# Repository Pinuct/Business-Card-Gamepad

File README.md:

# Business-Card-Gamepad
Hardware and software files for the Business Card Gamepad.

**IF YOU WANT MORE DETAILS ABOUT THE PROJET  ----->  [HACKADAY.IO](https://hackaday.io/project/28516-business-card-gamepad) <-----**

It contains all necesary files to make a Business Card Gamepad. With capacitive touch buttons and USB interface thought a USB micro B PCB connector. If you connect it to a PC with a USB to micro USB cable, it acts as a joystick for the host PC.

# Folders

## Arduino Code

Contains the Arduino project for the gamepad code of the business card and a touch button library (used to detect capacitive button press). The code of the .ino is simple and self explanatory, it it initializes the joystick library and the touch buttons library and loops throught the readings of the touch buttons, when there is a press it send a joystick event to the PC.

If you want to compile this code you will need to include two more libraries. This code can't not work without the great libreries that Martin Pittermann ([ADCTouch library](https://github.com/martin2250/ADCTouch)) and Matthew Heironimus ([ArduinoJoystickLibrary](https://github.com/MHeironimus/ArduinoJoystickLibrary)) did. So thanks to them to make this posible.

## Eagle PCB 

Contains an Eagle 7.50 project for the business card PCB. If you want to make it, is necesary to use a PCB of 0.6 mm thickness, needed for the USB PCB connector to be able to connect to a USB micro b cable.

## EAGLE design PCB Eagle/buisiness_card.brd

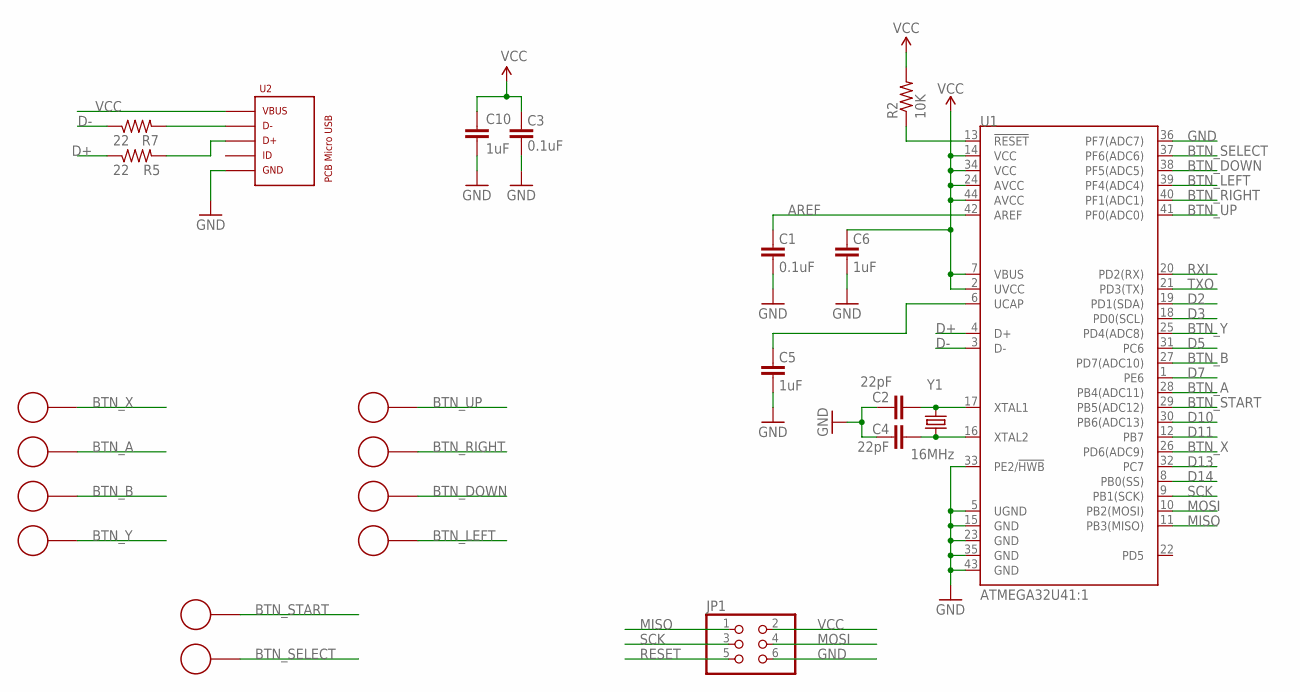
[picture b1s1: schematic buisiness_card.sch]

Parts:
B1, B2, B3, B4, B5, B6, B7, B8, B9, B10: CAPACITIVE_BUTTON; ROUND_CAP_BUTTON
C1, C3: 0.1uF; 0603-CAP
C2, C4: 22pF; 0603-CAP
C5, C6, C10: 1uF; 0603-CAP
JP1: PINHD-2X3; 2X03
R2: 10K; 0603-RES
R5, R7: 22; 0603-RES
U1: ATMEGA32U41:1; QFN-44-NOPAD_1:1
U2: PCB_MICRO_USB_BSS_2; USB_TYPE_B_SS_2
Y1: 16MHz; CRYSTAL-SMD-5X3

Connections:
AREF: C1.2, U1.42 (AREF)
BTN_A: B2.P$1, U1.28 (PB4(ADC11))
BTN_B: B3.P$1, U1.27 (PD7(ADC10))
BTN_DOWN: B7.P$1, U1.38 (PF5(ADC5))
BTN_LEFT: B8.P$1, U1.39 (PF4(ADC4))
BTN_RIGHT: B6.P$1, U1.40 (PF1(ADC1))
BTN_SELECT: B10.P$1, U1.37 (PF6(ADC6))
BTN_START: B9.P$1, U1.29 (PB5(ADC12))
BTN_UP: B5.P$1, U1.41 (PF0(ADC0))
BTN_X: B1.P$1, U1.26 (PD6(ADC9))
BTN_Y: B4.P$1, U1.25 (PD4(ADC8))
D2: U1.19 (PD1(SDA))
D3: U1.18 (PD0(SCL))
D5: U1.31 (PC6)
D7: U1.1 (PE6)
D10: U1.30 (PB6(ADC13))
D11: U1.12 (PB7)
D13: U1.32 (PC7)
D14: U1.8 (PB0(SS))
D+: R5.1, U1.4 (D+)
D-: R7.1, U1.3 (D-)
GND: C1.1, C2.2, C3.1, C4.2, C5.1, C6.1, C10.2, JP1.6, U1.5 (UGND), U1.15 (GND), U1.23 (GND), U1.33 (PE2/!HWB), U1.35 (GND), U1.36 (PF7(ADC7)), U1.43 (GND), U2.5
MISO: JP1.1, U1.11 (PB3(MISO))
MOSI: JP1.4, U1.10 (PB2(MOSI))
unnamed: C4.1, U1.16 (XTAL2), Y1.1
unnamed: C2.1, U1.17 (XTAL1), Y1.3 (2)
unnamed: C5.2, U1.6 (UCAP)
unnamed: R7.2, U2.2
unnamed: R5.2, U2.3
RESET: JP1.5, R2.1, U1.13 (!RESET)
RXI: U1.20 (PD2(RX))
SCK: JP1.3, U1.9 (PB1(SCK))
TXO: U1.21 (PD3(TX))
VCC: C3.2, C6.2, C10.1, JP1.2, R2.2, U1.2 (UVCC), U1.7 (VBUS), U1.14 (VCC), U1.24 (AVCC), U1.34 (VCC), U1.44 (AVCC), U2.1

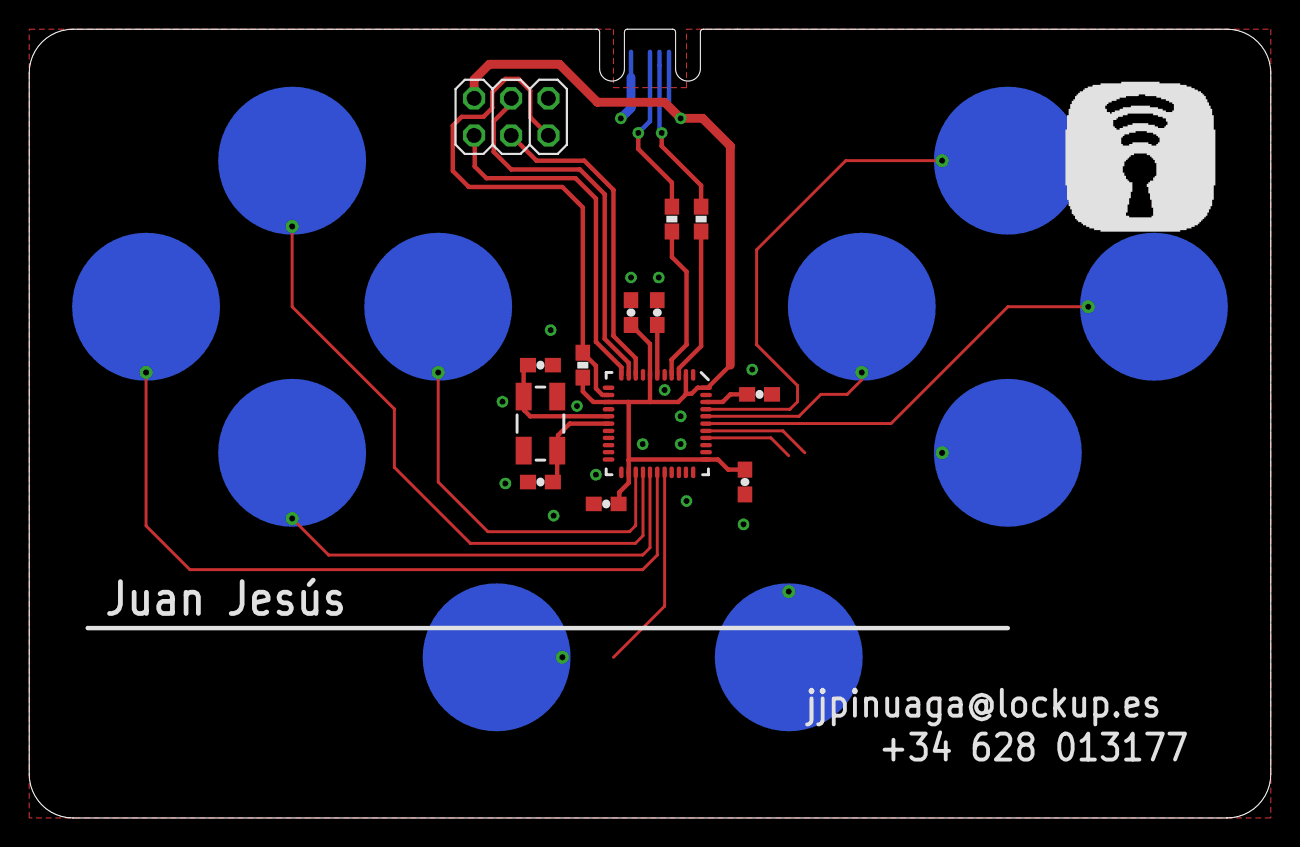
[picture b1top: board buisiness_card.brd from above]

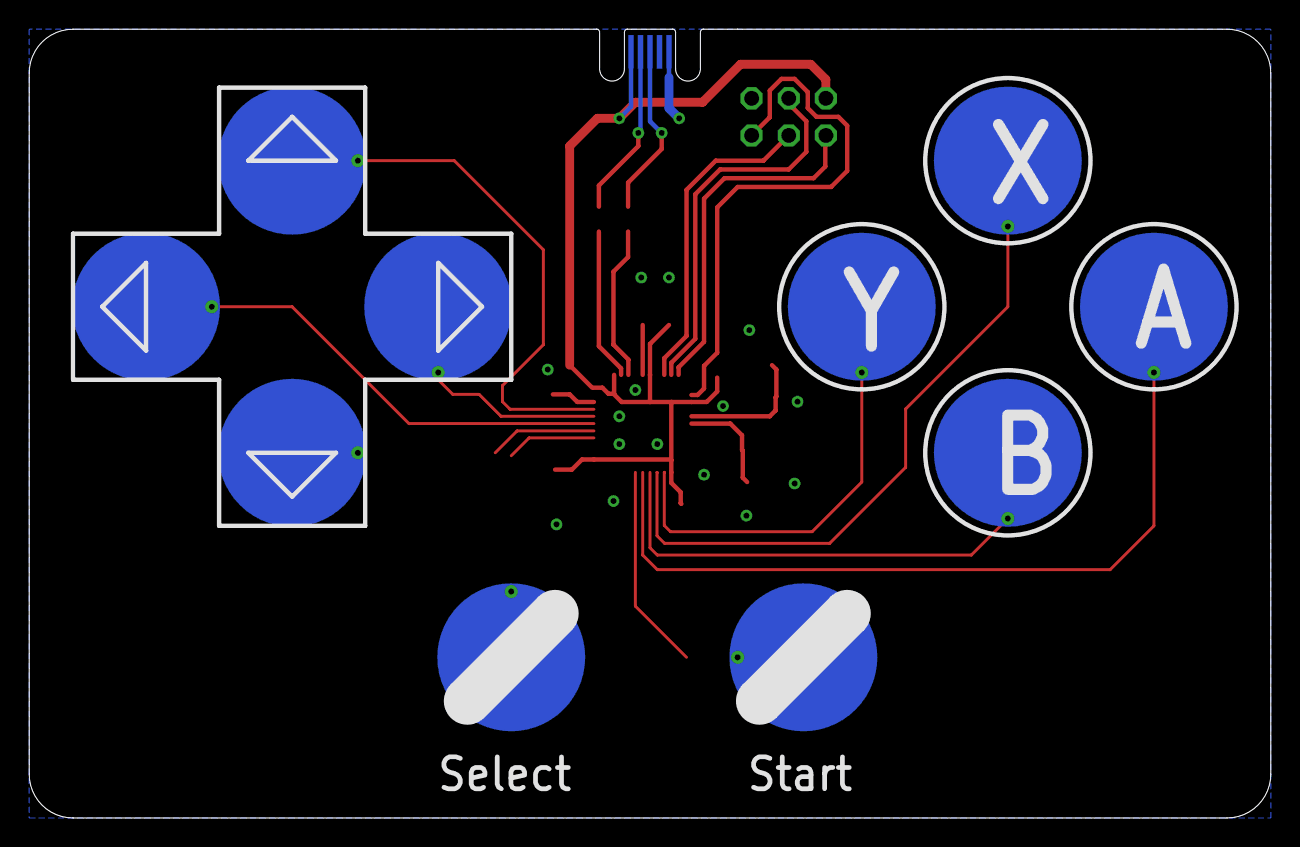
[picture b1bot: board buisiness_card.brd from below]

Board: 2 copper layers, 85.0 x 54.0 mm, 24 parts (11 on the bottom side), 24 nets.

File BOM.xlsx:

| Parts | Qty | Value | Description | Package | Note | Reference example
 | JP1 | 1 |  | PIN HEADER | 2X03 | DNM
 | C1, C3 | 2 | 0.1uF | 0603 0.1uF Capacitor | 0603
 | R2 | 1 | 10K ohm | 0603 10K ohm Resistor | 0603
 | Y1 | 1 | 16MHz | 16 Mhz Crystal 5x3.2 mm | CRYSTAL-SMD-5X3 |  | ABM3B-16.000MHZ-10-1-U-T
 | C5, C6, C10 | 3 | 1uF | 0603 1uF Capacitor | 0603
 | R5, R7 | 2 | 22 ohm | 0603 2 ohm Resistor | 0603
 | C2, C4 | 2 | 22pF | 0603 22pF Capacitor | 0603
 | U1 | 1 | ATMEGA32U4 | Atmel 44-pin 8-bit Microcontroller with 32KBytes of ISP Flash and USB Controller | QFN-44 |  | ATMEGA32U4-MU
 | B1, B2, B3, B4, B5, B6, B7, B8, B9, B10 | 10 | CAPACITIVE_BUTTON | Copper pads for capacitive buttons | - | DNM
 | U2 | 1 | PCB_MICRO_USB_BSS_2 | PCB USB micro b connector | - | DNM
 |  |  |  | DNM -> Do Not Mount

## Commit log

2017-12-12 Uploaded Eagle PCB files and Arduino code files.
2017-12-29 Added BOM and updated components references.

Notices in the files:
README.md:
License: CC BY 4.0
parts and their libraries:
SparkFun-DigitalIC: Licensing: Creative Commons ShareAlike 4.0 International - https://creativecommons.org/licenses/by-sa/4.0
